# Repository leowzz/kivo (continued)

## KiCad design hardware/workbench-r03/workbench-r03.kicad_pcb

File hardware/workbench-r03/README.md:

# Kivo Workbench r03 PCB Draft

This is an editable electrical and placement draft, **not a board ready to
order**. Open `workbench-r03.kicad_pro` in KiCad 10. The PCB is intentionally
unrouted, and no Gerber, drill, or assembly-order files are provided.

## Confirmed Scope

- RP2040 chip directly on the main PCB, with factory assembly for the QFN.
- 18 ordinary MX switches with Kailh-style hot-swap sockets on the PCB back.
- USB-C for USB 2.0 device data and 5 V power.
- Existing SH1106, EC11, encoder press, confirm and back module connected by a
  harness. The module remains a separate panel-mounted assembly.
- Enclosure changes and reprinting are permitted.

The existing `r02` product YAML remains the source of the GPIO mapping. `r03`
here is a proposed new hardware revision, not a released Product Version ID.

## Files

| File | Purpose |
| --- | --- |
| `workbench-r03.kicad_sch` | Embedded-symbol schematic, 59 components |
| `workbench-r03.kicad_pcb` | Four-layer, 1.6 mm placement draft with 18 bottom sockets |
| `workbench-r03.kicad_pro` | KiCad project and preliminary design rules |
| `Workbench.pretty/` | Local hot-swap socket and measured-head mounting footprints |
| `key-coordinates.csv` | Model panel coordinates and PCB coordinates, in mm |
| `placement.json` | Reproducible placement and pin-to-net manifest |
| `bom-draft.csv` | Uncosted component list; not a factory purchasing BOM |
| `verification.md` | Checks performed and open issues |

## Electrical Design

The RP2040 core follows the Raspberry Pi hardware design guide: 3.3 V I/O,
the internal 1.1 V regulator feeding DVDD, TESTEN tied to ground, local bypass
capacitors, QSPI flash, and an external 12 MHz crystal. The proposed parts are:

| Function | Proposed part / connection |
| --- | --- |
| MCU | RP2040, QFN-56 with exposed ground pad |
| Flash | W25Q128JVSIQ, 128 Mbit / 16 MiB, 208 mil SOIC-8 |
| Crystal | Abracon ABM8-272-T3, 12 MHz, 15 pF loads, 1 kohm damping resistor |
| 3.3 V regulator | AP2112K-3.3TRG1, 1 uF input and 4.7 uF output |
| USB-C | GCT USB4105-GF-A, USB 2.0, separate 5.1 kohm CC1/CC2 pull-downs |
| USB data | USBLC6-2SC6 protection, 27 ohm series resistors near RP2040 |
| BOOTSEL | Push switch through 1 kohm to QSPI_SS; 10 kohm pull-up fitted |
| RESET | Push switch to RUN, with 10 kohm pull-up |
| Keys | Each GPIO to one socket contact; the other contact to GND |
| I2C pull-ups | R9/R10 4.7 kohm footprints, DNP pending module inspection |

Direct GPIO inputs use the existing firmware's pull-ups and debounce. This
topology does not need matrix diodes. The 16 MiB flash matches the current
YD-RP2040 build's maximum flash size. That does not, by itself, validate the
custom board's firmware identity or boot behavior.

These are proposed MPNs, not a stock-checked shopping list. In particular,
confirm the purchased socket's drawing against the vendored footprint, and
confirm the exact USB connector suffix, plating and packaging before ordering.
The PCB includes no microphone, speaker, battery, charger or RGB lighting.

## Main Board Interfaces

J2 is a **main-board harness pinout chosen for this PCB**. It is not evidence of
the left-to-right pin order of the purchased display module. Use individually
mapped wires and the module's labels; do not assume a straight-through cable.
The repository's YAML provides the GPIO assignments below, but does not record
the module connector numbering or power specification.

| J2 Pin | Main Board Signal | RP2040 GPIO |
| --- | --- | --- |
| 1 (square pad) | GND | - |
| 2 | 3.3 V | - |
| 3 | SCL | 27 |
| 4 | SDA | 26 |
| 5 | Confirm / OK | 22 |
| 6 | Encoder press | 28 |
| 7 | Encoder A | 21 |
| 8 | Encoder B | 20 |
| 9 | Back | 19 |

The main-board header is a 1x9, 2.54 mm pitch header. It is placed vertically
in the PCB top view with pin 1 closest to the USB edge. J2 provides **3.3 V only**;
verify the module operates at 3.3 V and that its signals and I2C pull-ups do not
drive 5 V into the RP2040. R9/R10 should be fitted only if the module lacks
suitable pull-ups. The guide's "seven GPIO" count excludes power and ground.

J3 pins 1-4 are 3.3 V reference, GND, SWDIO and SWCLK. A debugger should sense
the target voltage without powering a simultaneously USB-powered board.

J4 exposes all five unused RP2040 GPIOs at the **rear-left (upper-left in top
view)** of the PCB. It is a 1x7 plated through-hole header, 2.54 mm pitch with
1.0 mm drills. Viewed from the component side with USB at the top, pin 1 is
the leftmost square pad; the pins run left to right:

| J4 Pin | Signal |
| --- | --- |
| 1 (square pad) | GND |
| 2 | 3.3 V |
| 3 | GPIO0 |
| 4 | GPIO23 |
| 5 | GPIO24 |
| 6 | GPIO25 |
| 7 | GPIO29 / ADC3 |

These pins connect directly to the RP2040 and use **3.3 V logic, not 5 V**.
External loads must fit within the regulator's remaining current and thermal
budget. GPIO24/25 are free on this bare-chip design, but the current YD-RP2040
firmware pin whitelist excludes them. Enable them in the future custom-board
definition before use; this hardware change does not change the product
profile or assign functions to any expansion pins.

J5 (BOOT) and J6 (RESET) sit immediately to the left of the rear USB-C port.
Each is a 1x2 plated through-hole footprint, 2.54 mm pitch with 1.0 mm drills,
for a matching normally-open momentary button or short wires to a button.
They are not a universal four-leg tactile-switch footprint. Viewed from the
component side with USB at the top, pin 1 is the left square pad:

| Header | Pin 1 | Pin 2 | Connection |
| --- | --- | --- | --- |
| J5 BOOT | BOOT_BUTTON | GND | Parallel to SW19; through R7 (1 kohm) to QSPI_SS |
| J6 RESET | RUN | GND | Parallel to SW20; R8 (10 kohm) pulls RUN up to 3.3 V |

The onboard SW19/SW20 buttons remain fitted. To enter the USB bootloader,
hold BOOT, press and release RESET, then release BOOT. Do not short QSPI_SS
directly to ground; J5 preserves the existing series resistor.

K1-K18 retain GPIO1-GPIO18. Viewed from the key side with USB at the back,
K1-K6 are the row closest to the display, K7-K12 are the middle row, and K13-K18
are closest to the user. The geometry script does not assign key IDs; this
numbering follows the current product layout's reading order.

## Mechanical Basis

Source: `scripts/modeling/integrated_workstation.py`, specifically
`KEY_COLUMNS`, `KEY_ROWS`, `KEY_PITCH`, `KEY_X0`, `KEY_Y0`, `PANEL_X0`, and
`PANEL_Y0`. The generated switch centers use the **flat panel plane**, not a
top-down projection of its 30-degree assembled position.

- Existing panel: 132 x 117 mm, tilted 30 degrees.
- Proposed board: 126 x 105 mm, 1.6 mm thick, parallel to the panel.
- Model panel coordinates: X to the right, Y from the front towards the rear.
- Board coordinates in CSV: origin at the board's rear-left corner, X right,
  Y towards the user. Conversion: `pcb_x = panel_x - 3`,
  `pcb_y = 113 - panel_y`.
- The KiCad page uses an additional (50, 50) mm translation for readability.
- 19.05 mm switch pitch is preserved. The five 3.4 mm PCB holes are **new**
  proposed mounting positions; they do not reuse the existing panel screw axes.
- The local mounting footprint assumes a screw head no larger than 5.6 mm,
  with a 6.0 mm clearance envelope and no large washer. This follows the
  project's measured 5.3 mm head, but actual fasteners and bosses need checking.

The current shell has two solid support walls in the key field, six fly-wire
clips, a bottom-mounted development-board cradle and low rear USB openings.
These features require redesign around the new board. The existing two-switch
pod also needs a decision during the enclosure revision because it is absent
from the current product's electrical configuration.

The `Dwgs.User` display rectangle is a reserved area, not a validated 3D module
model. Before final PCB dimensions, verify the switch plate-to-PCB distance,
socket underside height, display connector height, panel screw access and USB
plug insertion. Include the J4 header/mating connector height near the display
and the J5/J6 button or wire clearance in the enclosure check. The new USB port
follows the sloped board and cannot align with
the old bottom-board USB opening. The existing eight-pin modeling constant is
inconsistent with the apparent nine contacts in `refer/dsp-encp.png`; keep the
electrical harness independent of that mechanical assumption.

## Remaining Design Work

1. Verify the actual display module's voltage, connector labels and pull-ups,
   and the exact socket and USB connector drawings.
2. Establish a manufacturer stackup and impedance geometry. The four-layer
   board is proposed to give USB and the RP2040 a continuous reference plane;
   the current layer count is not a validated impedance specification.
3. Complete placement for short crystal, QSPI, regulator and decoupling paths,
   then route, pour ground planes and rerun DRC. Keep the USB pair over continuous
   ground and determine widths/gap for 90 ohm differential impedance from the
   selected stackup. Review QFN ground and paste/thermal-via assembly details.
4. Revise and collision-check the enclosure in 3D, including MX plate capture
   thickness, new PCB mounts and the USB opening. Existing STLs are unchanged.
5. Add the new board identity/build target and an r03 product definition when
   the electrical design is frozen; validate USB descriptors, flash size,
   BOOTSEL, reset, HID/CDC, all 18 keys, display and controls on assembled boards.
6. Select purchasable parts, complete ERC/DRC and assembly review, and then
   export Gerbers, drill files, BOM and placement files for the board house.

## Reproduction

The checked-in KiCad files are the editable design. The generators are a way to
reproduce this first draft, not a substitute for the PCB editor. Generate into a
new directory to preserve manual changes:

```sh
uv run --script scripts/hardware/generate_workbench.py --output /tmp/workbench-review
```

Copy `Workbench.pretty`, `3dmodels`, `fp-lib-table` and the project settings from
this directory into that new directory, then run the placement script using
KiCad's bundled Python interpreter:

```sh
/Applications/KiCad/KiCad.app/Contents/Frameworks/Python.framework/Versions/3.9/bin/python3.9 \
  scripts/hardware/place_workbench.py /tmp/workbench-review/placement.json \
  /tmp/workbench-review/workbench-r03.kicad_pcb
```

The placement script refuses to overwrite an existing PCB. Both scripts accept
explicit library paths for KiCad installations at other locations.

## Sources

- Existing product: `products/kivo-workbench-rp-k18-disp-encp-r02/product.yaml`.
- [Raspberry Pi Hardware Design with RP2040](https://datasheets.raspberrypi.com/rp2040/hardware-design-with-rp2040.pdf), release 2,
  sections 2.1-2.4. The source reference design's routing was not transplanted.
- [foostan/kbd MX hot-swap footprint](https://github.com/foostan/kbd/blob/main/kicad-footprints/kbd.pretty/keyswitch_cherrymx_hotswap_1u.kicad_mod),
  retrieved 2026-09-05, upstream blob `3601d4e1d8f8c5b49b9d56c87e00ec56cd4921a1`.
  Only its 3D-model path was changed. The matching socket STEP model is vendored
  from the same repository. License: `licenses/foostan-kbd-MIT.txt`.
- Standard electronic symbols, packages and 3D models come from installed
  KiCad 10.0.6 libraries. The schematic embeds the symbols for portability.

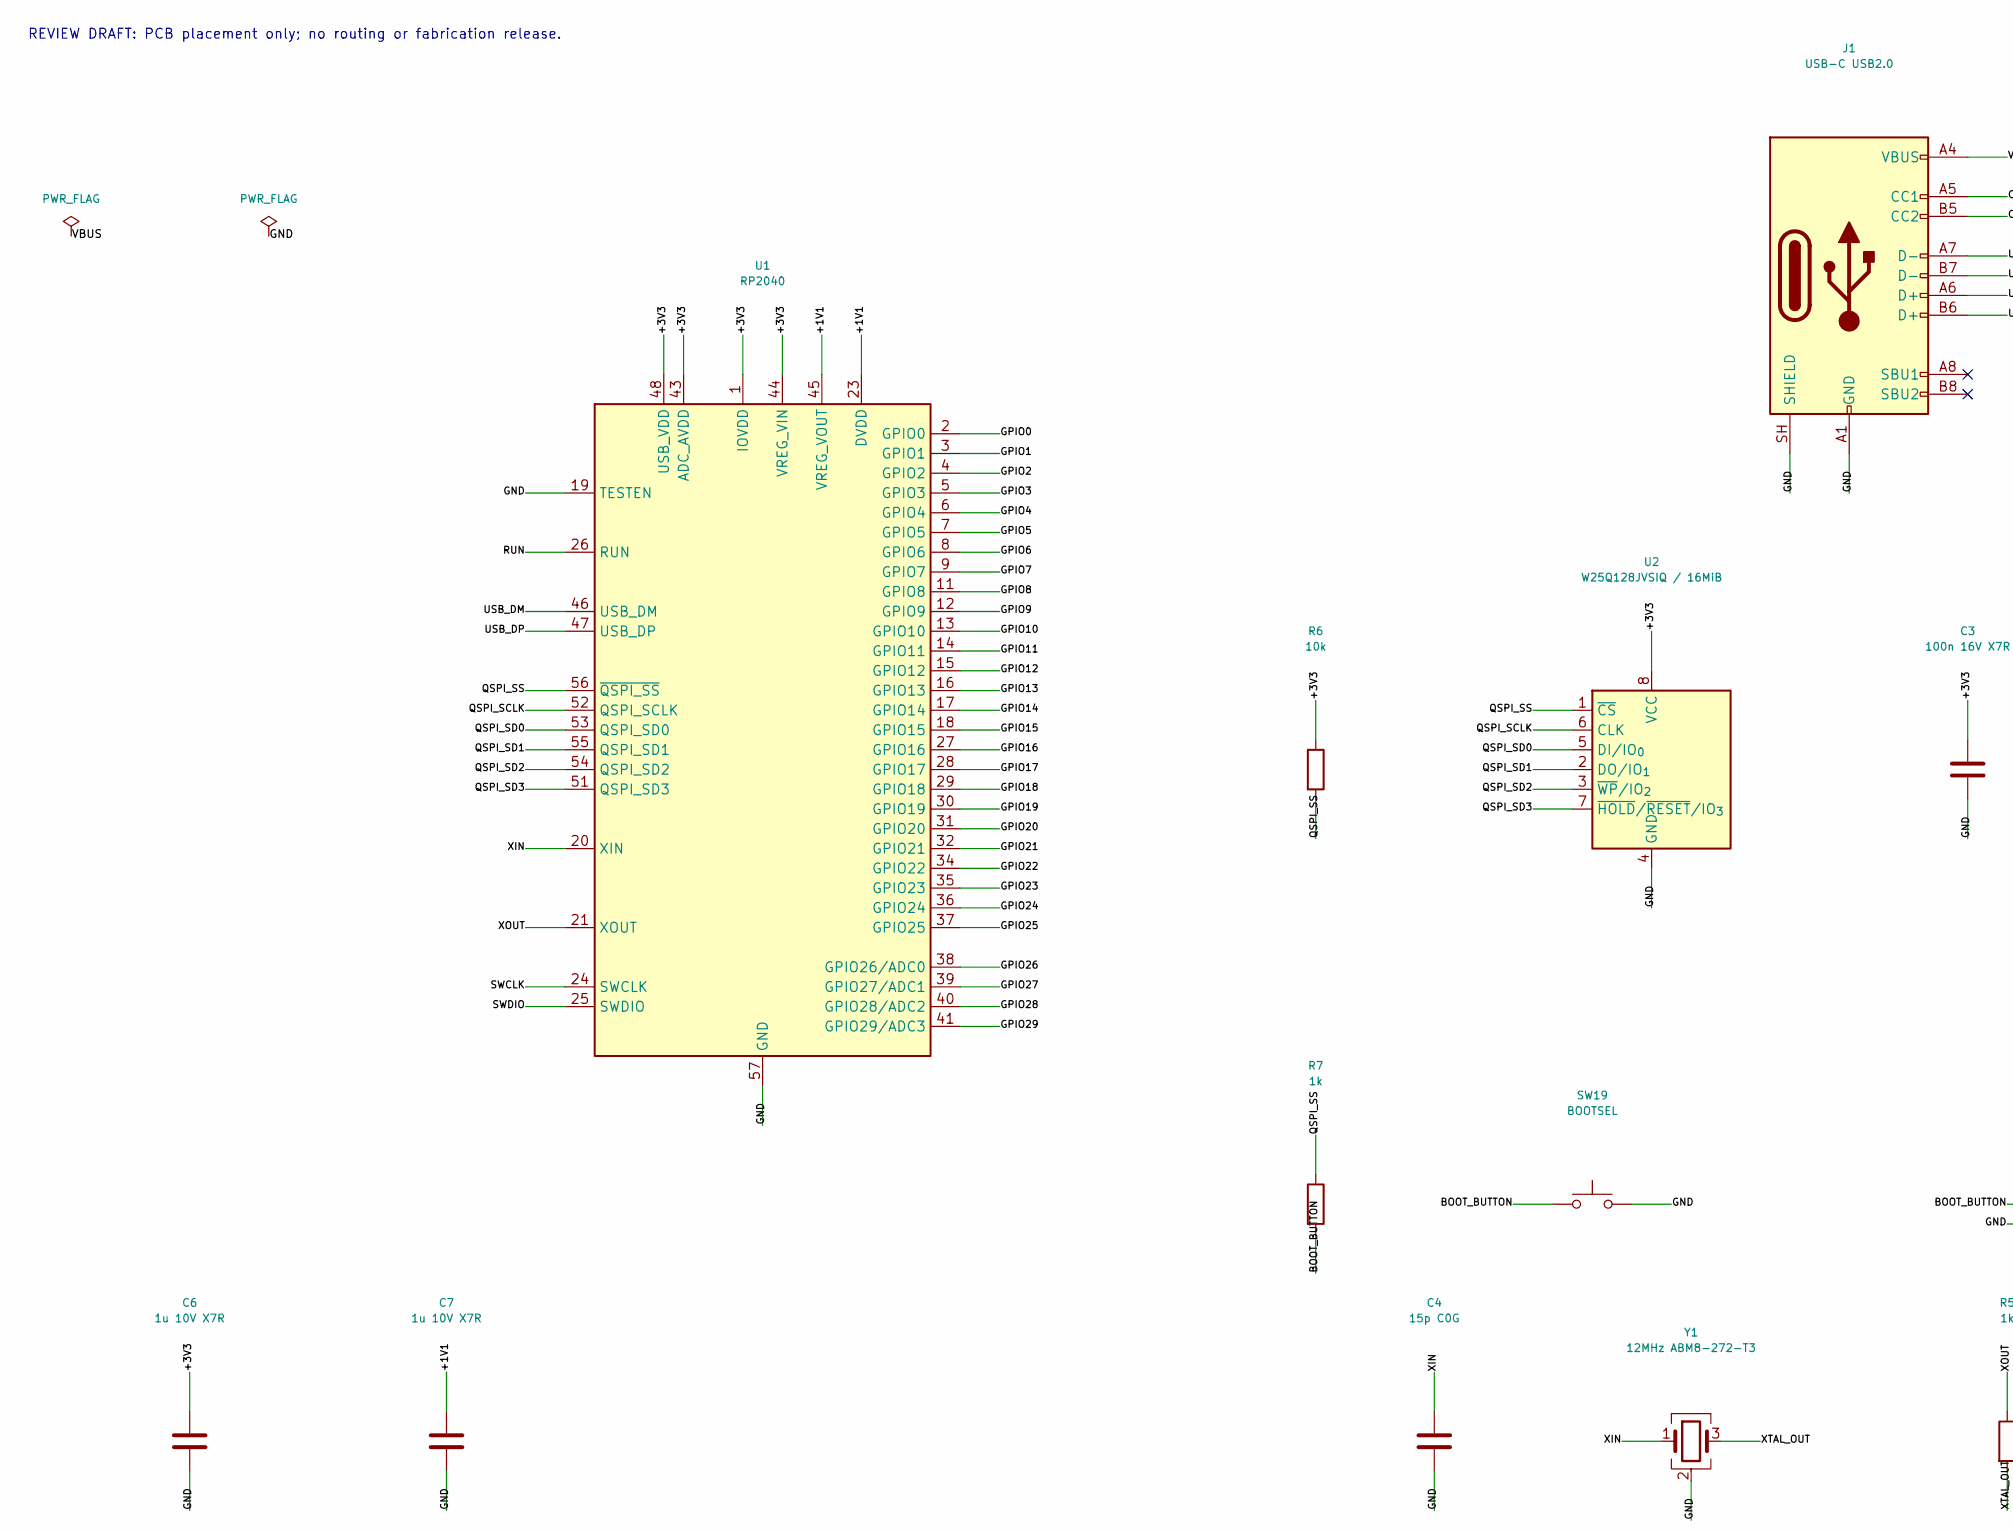
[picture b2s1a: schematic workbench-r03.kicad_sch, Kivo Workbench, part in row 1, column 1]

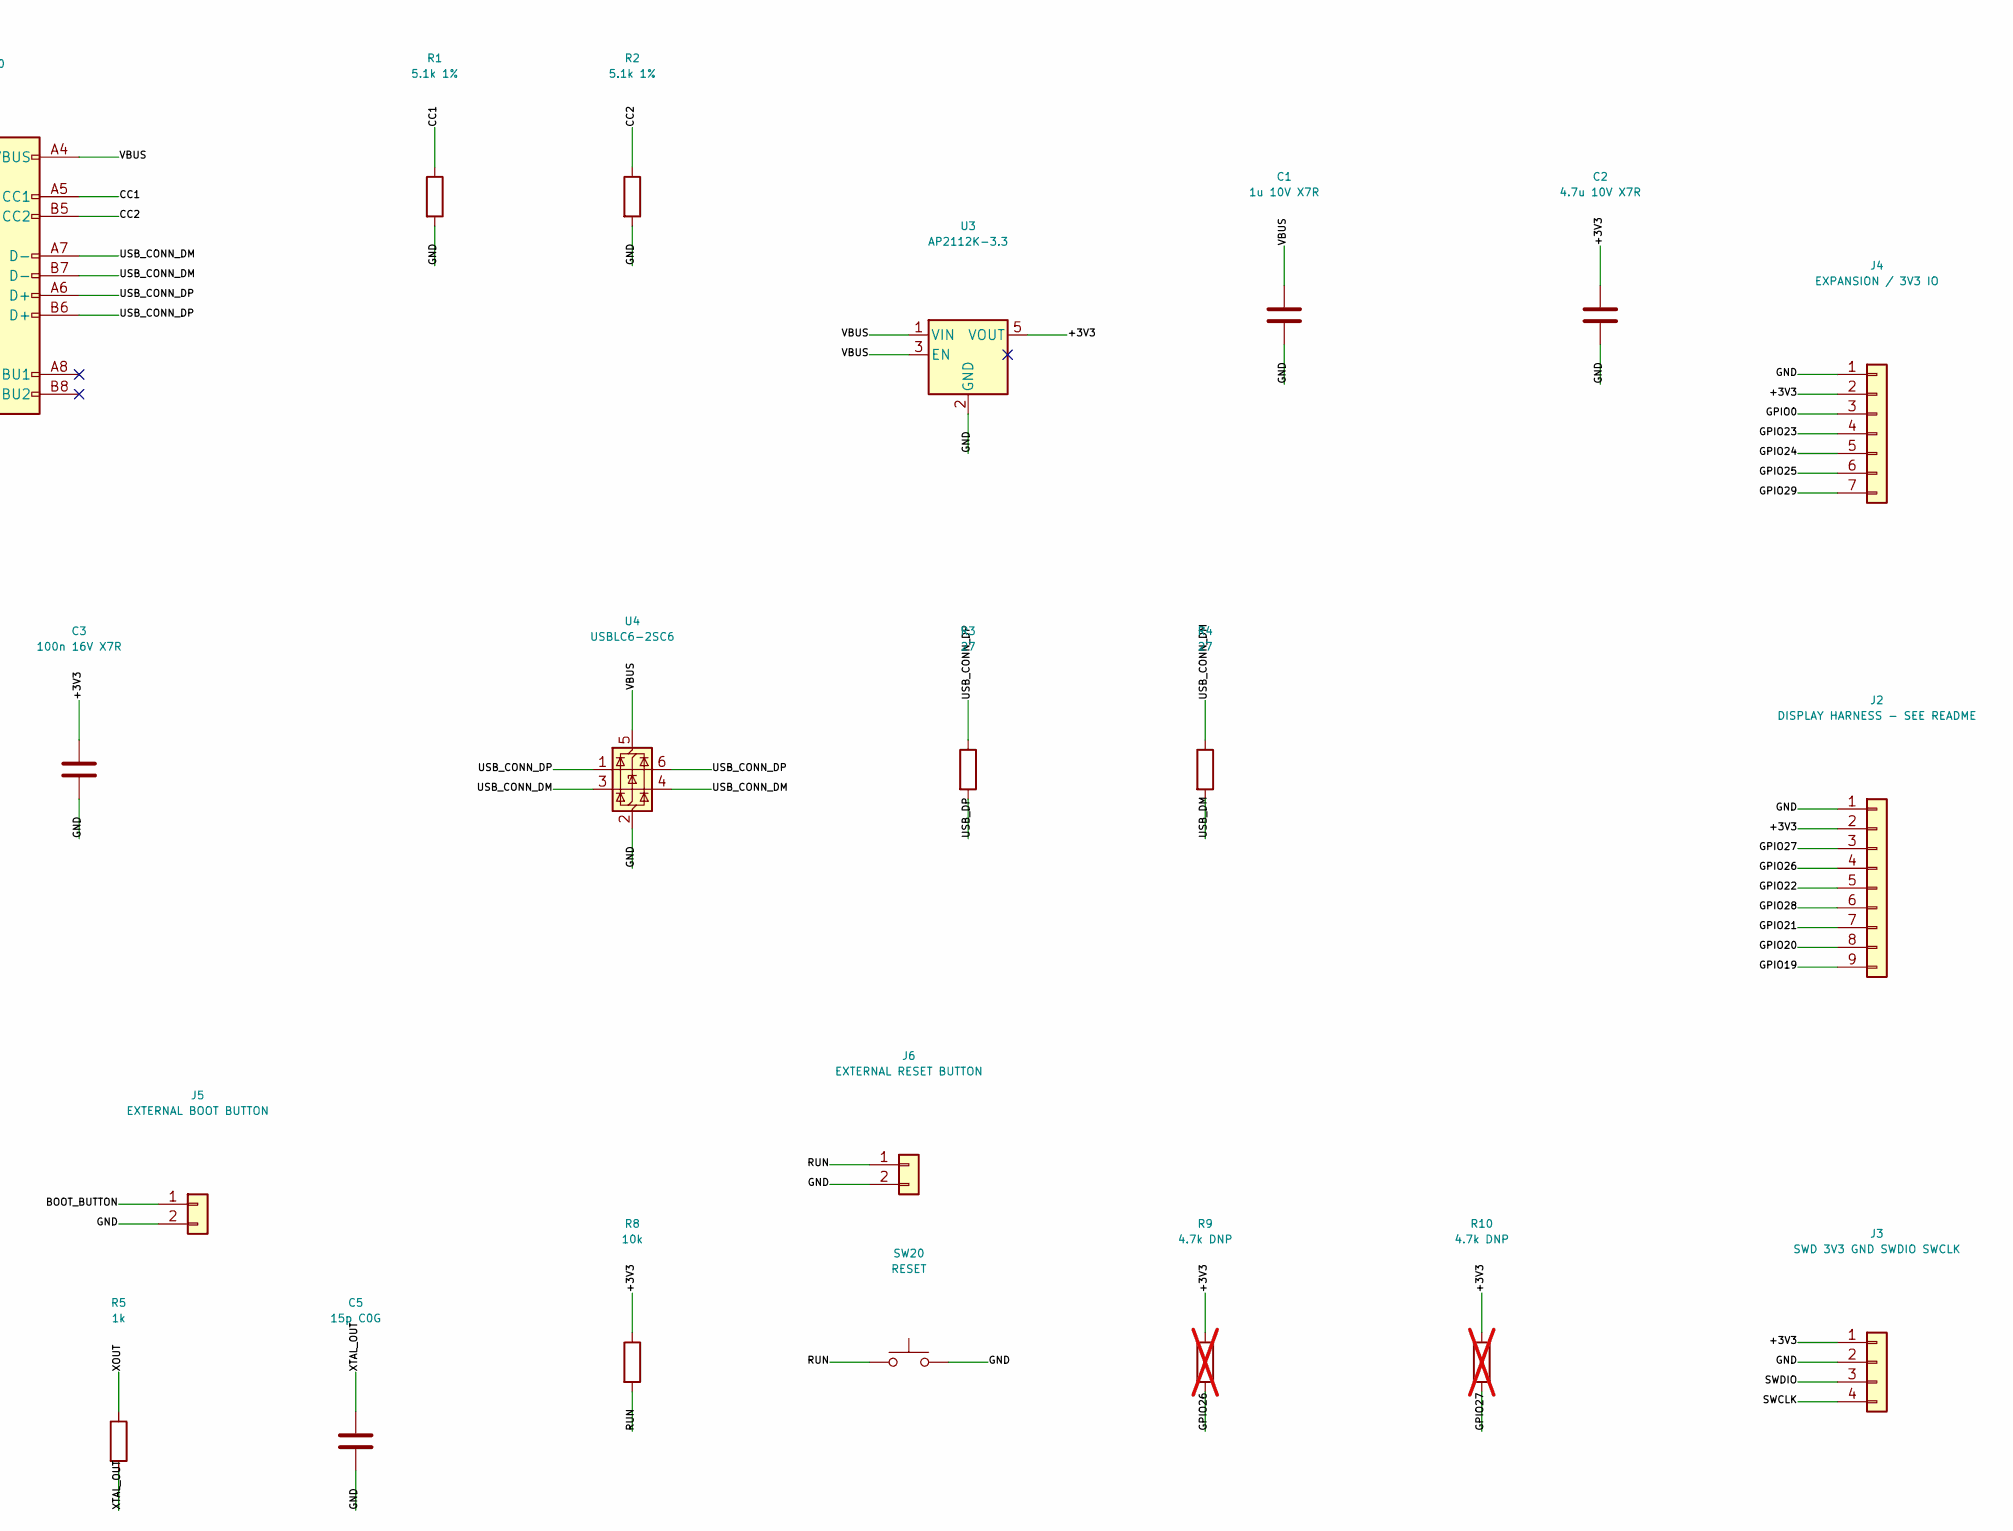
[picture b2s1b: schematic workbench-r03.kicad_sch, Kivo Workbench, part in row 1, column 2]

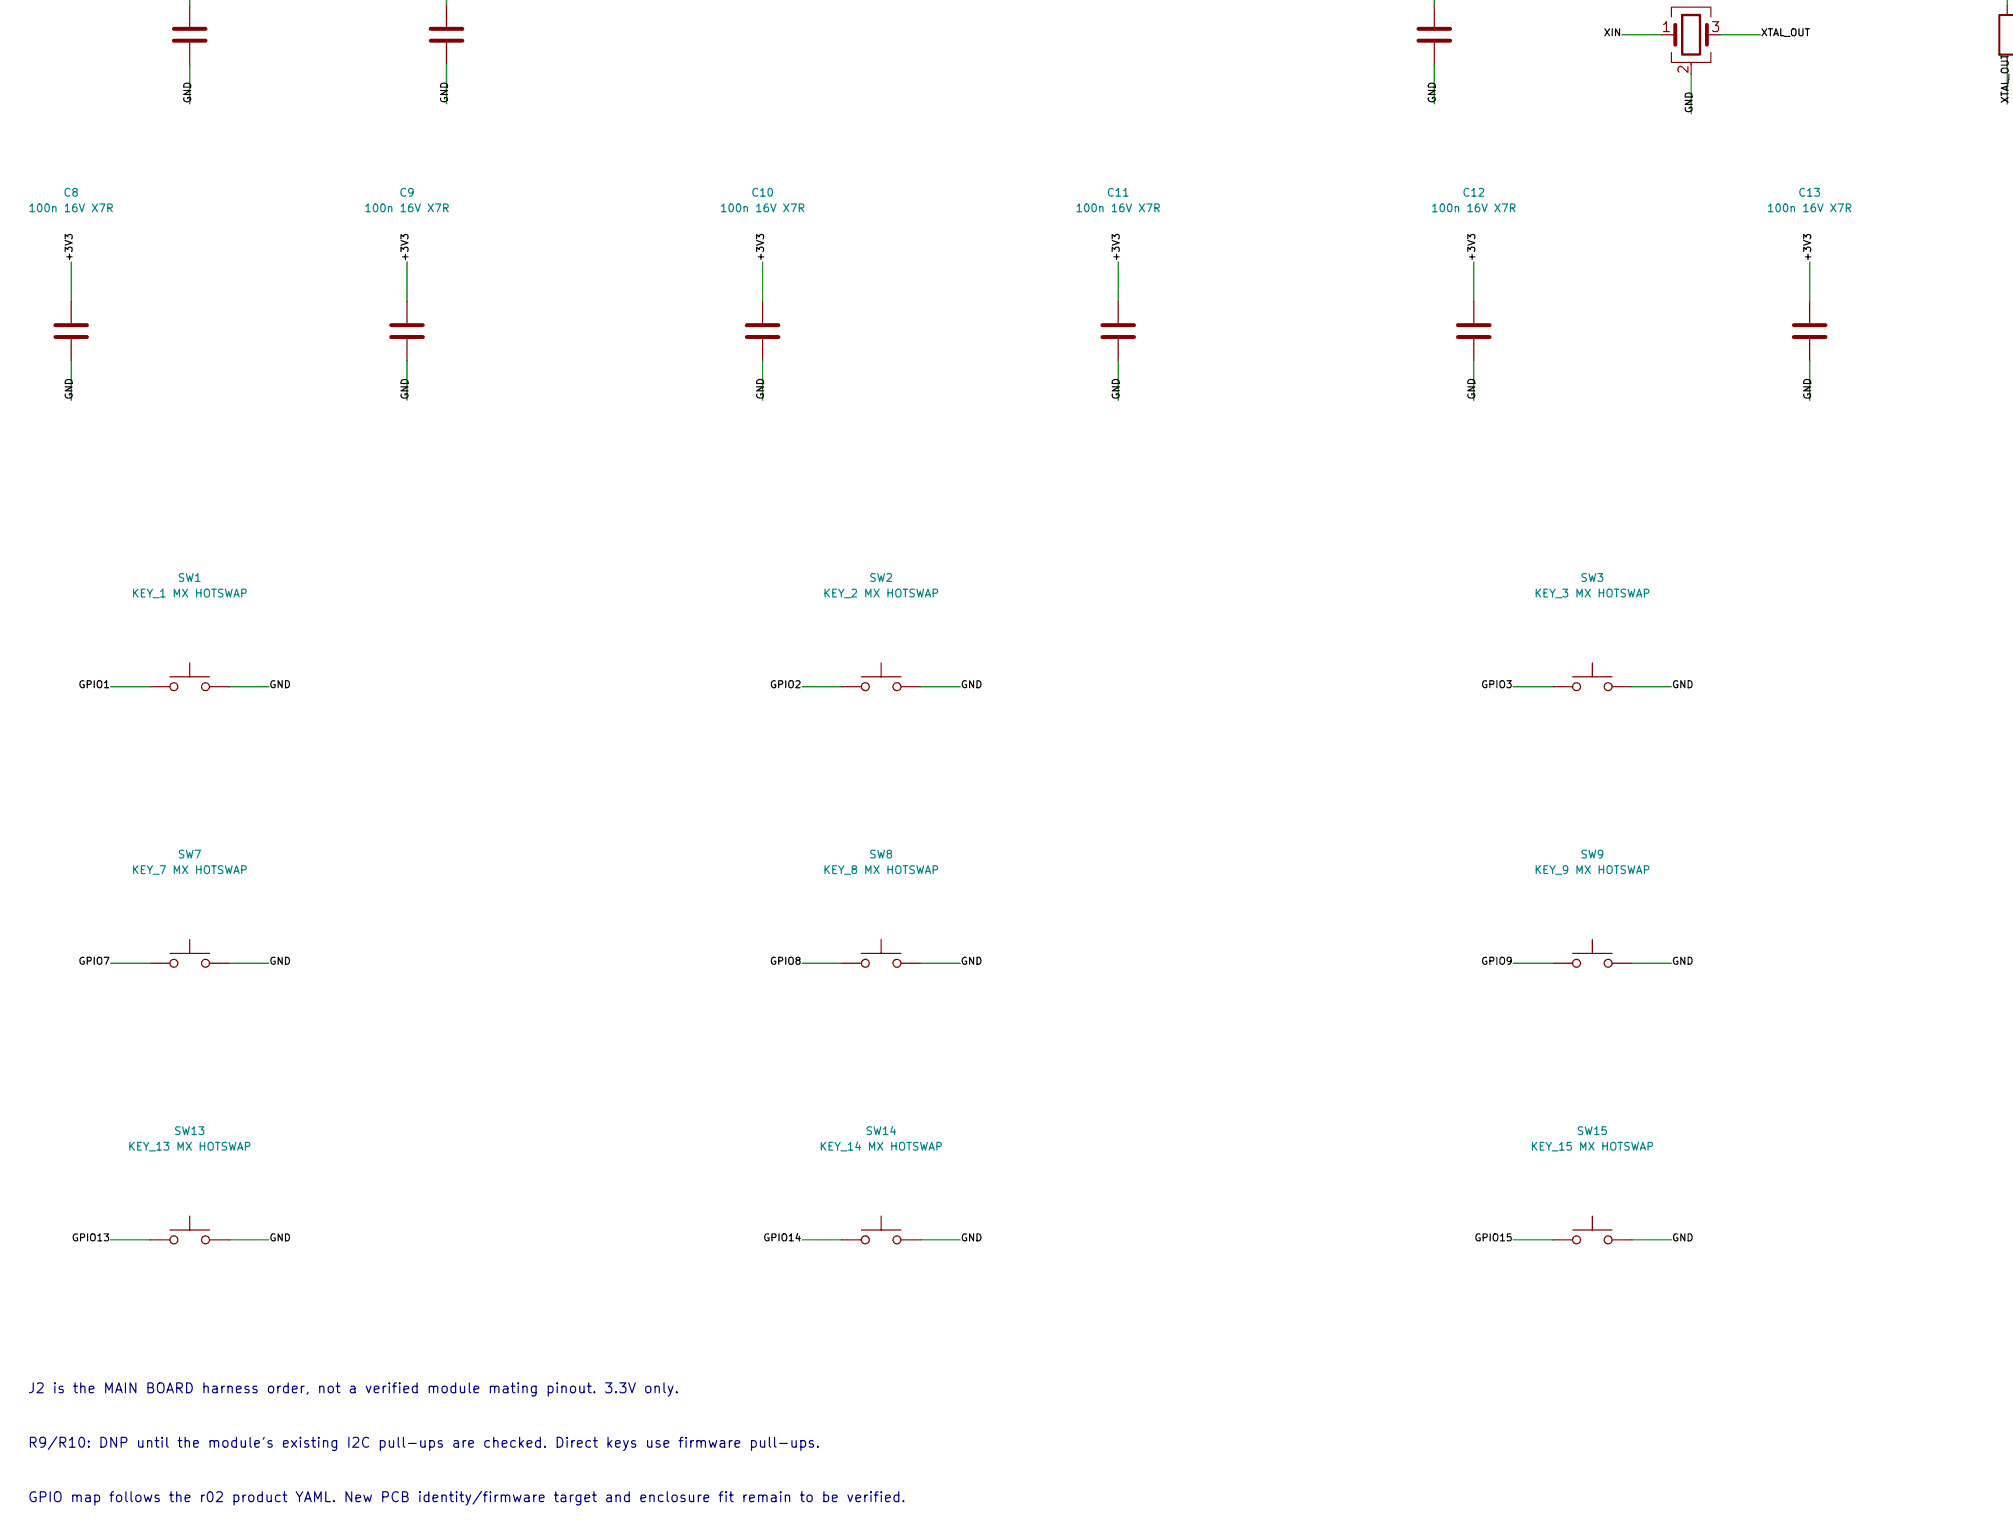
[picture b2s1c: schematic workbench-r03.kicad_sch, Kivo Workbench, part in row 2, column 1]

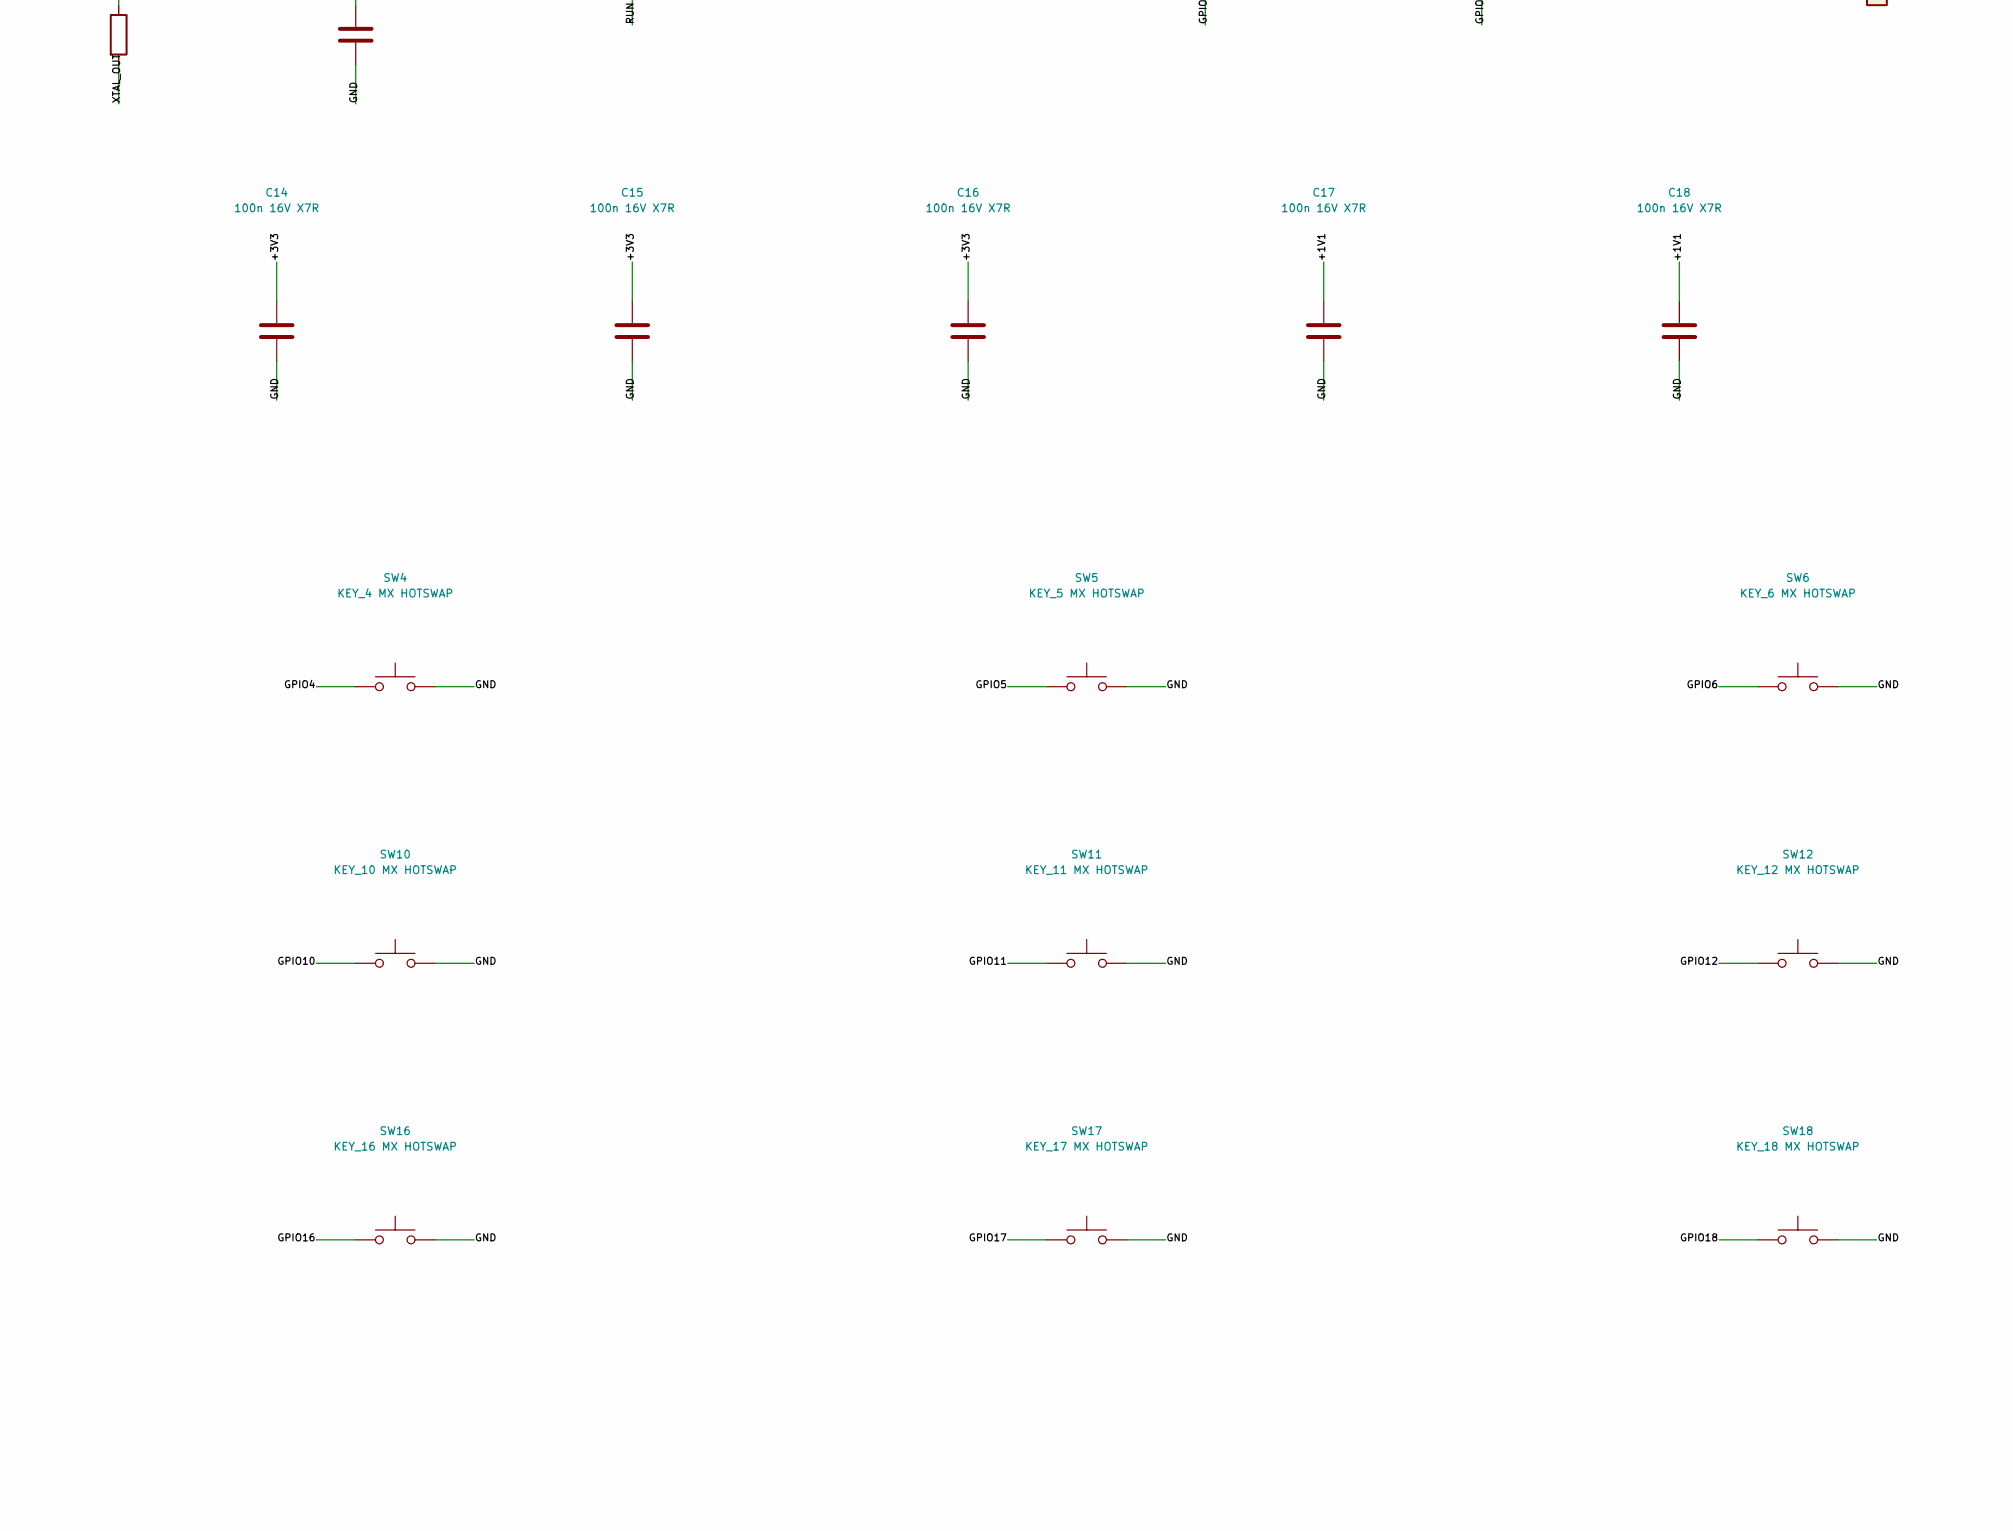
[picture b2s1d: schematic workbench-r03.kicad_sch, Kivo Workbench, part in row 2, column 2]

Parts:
C1: 1u 10V X7R; C_0603_1608Metric
C2: 4.7u 10V X7R; C_0603_1608Metric
C3, C8, C9, C10, C11, C12, C13, C14, C15, C16, C17, C18: 100n 16V X7R; C_0402_1005Metric
C4, C5: 15p C0G; C_0402_1005Metric
C6, C7: 1u 10V X7R; C_0402_1005Metric
J1: USB-C USB2.0; USB_C_Receptacle_GCT_USB4105-xx-A_16P_TopMnt_Horizontal
J2: DISPLAY HARNESS - SEE README; PinHeader_1x09_P2.54mm_Vertical
J3: SWD 3V3 GND SWDIO SWCLK; PinHeader_1x04_P2.54mm_Vertical
J4: EXPANSION / 3V3 IO; PinHeader_1x07_P2.54mm_Vertical
J5: EXTERNAL BOOT BUTTON; PinHeader_1x02_P2.54mm_Vertical
J6: EXTERNAL RESET BUTTON; PinHeader_1x02_P2.54mm_Vertical
R1, R2: 5.1k 1%; R_0603_1608Metric
R3, R4: 27; R_0603_1608Metric
R5, R7: 1k; R_0603_1608Metric
R6, R8: 10k; R_0603_1608Metric
R9, R10: 4.7k DNP; R_0603_1608Metric; not fitted
SW1: KEY_1 MX HOTSWAP; keyswitch_cherrymx_hotswap_1u
SW2: KEY_2 MX HOTSWAP; keyswitch_cherrymx_hotswap_1u
SW3: KEY_3 MX HOTSWAP; keyswitch_cherrymx_hotswap_1u
SW4: KEY_4 MX HOTSWAP; keyswitch_cherrymx_hotswap_1u
SW5: KEY_5 MX HOTSWAP; keyswitch_cherrymx_hotswap_1u
SW6: KEY_6 MX HOTSWAP; keyswitch_cherrymx_hotswap_1u
SW7: KEY_7 MX HOTSWAP; keyswitch_cherrymx_hotswap_1u
SW8: KEY_8 MX HOTSWAP; keyswitch_cherrymx_hotswap_1u
SW9: KEY_9 MX HOTSWAP; keyswitch_cherrymx_hotswap_1u
SW10: KEY_10 MX HOTSWAP; keyswitch_cherrymx_hotswap_1u
SW11: KEY_11 MX HOTSWAP; keyswitch_cherrymx_hotswap_1u
SW12: KEY_12 MX HOTSWAP; keyswitch_cherrymx_hotswap_1u
SW13: KEY_13 MX HOTSWAP; keyswitch_cherrymx_hotswap_1u
SW14: KEY_14 MX HOTSWAP; keyswitch_cherrymx_hotswap_1u
SW15: KEY_15 MX HOTSWAP; keyswitch_cherrymx_hotswap_1u
SW16: KEY_16 MX HOTSWAP; keyswitch_cherrymx_hotswap_1u
SW17: KEY_17 MX HOTSWAP; keyswitch_cherrymx_hotswap_1u
SW18: KEY_18 MX HOTSWAP; keyswitch_cherrymx_hotswap_1u
SW19: BOOTSEL; SW_SPST_TL3342
SW20: RESET; SW_SPST_TL3342
U1: RP2040; QFN-56-1EP_7x7mm_P0.4mm_EP3.2x3.2mm
U2: W25Q128JVSIQ / 16MiB; SOIC-8_5.3x5.3mm_P1.27mm
U3: AP2112K-3.3; SOT-23-5
U4: USBLC6-2SC6; SOT-23-6
Y1: 12MHz ABM8-272-T3; Crystal_SMD_3225-4Pin_3.2x2.5mm

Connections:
/+1V1: C7.1, C17.1, C18.1, U1.23 (DVDD), U1.45 (VREG_VOUT), U1.50 (DVDD)
/+3V3: C2.1, C3.1, C6.1, C8.1, C9.1, C10.1, C11.1, C12.1, C13.1, C14.1, C15.1, C16.1, J2.2, J3.1, J4.2, R6.1, R8.1, R9.1, R10.1, U1.1 (IOVDD), U1.10 (IOVDD), U1.22 (IOVDD), U1.33 (IOVDD), U1.42 (IOVDD), U1.43 (ADC_AVDD), U1.44 (VREG_VIN), U1.48 (USB_VDD), U1.49 (IOVDD), U2.8 (VCC), U3.5 (VOUT)
/BOOT_BUTTON: J5.1, R7.2, SW19.1
/CC1: J1.A5 (CC1), R1.1
/CC2: J1.B5 (CC2), R2.1
/GND: C1.2, C2.2, C3.2, C4.2, C5.2, C6.2, C7.2, C8.2, C9.2, C10.2, C11.2, C12.2, C13.2, C14.2, C15.2, C16.2, C17.2, C18.2, J1.A1 (GND), J1.A12 (GND), J1.B1 (GND), J1.B12 (GND), J1.SH (SHIELD), J2.1, J3.2, J4.1, J5.2, J6.2, R1.2, R2.2, SW1.2, SW2.2, SW3.2, SW4.2, SW5.2, SW6.2, SW7.2, SW8.2, SW9.2, SW10.2, SW11.2, SW12.2, SW13.2, SW14.2, SW15.2, SW16.2, SW17.2, SW18.2, SW19.2, SW20.2, U1.19 (TESTEN), U1.57 (GND), U2.4 (GND), U3.2 (GND), U4.2 (GND), Y1.2 (G), Y1.4 (G)
/GPIO0: J4.3, U1.2 (GPIO0)
/GPIO1: SW1.1, U1.3 (GPIO1)
/GPIO2: SW2.1, U1.4 (GPIO2)
/GPIO3: SW3.1, U1.5 (GPIO3)
/GPIO4: SW4.1, U1.6 (GPIO4)
/GPIO5: SW5.1, U1.7 (GPIO5)
/GPIO6: SW6.1, U1.8 (GPIO6)
/GPIO7: SW7.1, U1.9 (GPIO7)
/GPIO8: SW8.1, U1.11 (GPIO8)
/GPIO9: SW9.1, U1.12 (GPIO9)
/GPIO10: SW10.1, U1.13 (GPIO10)
/GPIO11: SW11.1, U1.14 (GPIO11)
/GPIO12: SW12.1, U1.15 (GPIO12)
/GPIO13: SW13.1, U1.16 (GPIO13)
/GPIO14: SW14.1, U1.17 (GPIO14)
/GPIO15: SW15.1, U1.18 (GPIO15)
/GPIO16: SW16.1, U1.27 (GPIO16)
/GPIO17: SW17.1, U1.28 (GPIO17)
/GPIO18: SW18.1, U1.29 (GPIO18)
/GPIO19: J2.9, U1.30 (GPIO19)
/GPIO20: J2.8, U1.31 (GPIO20)
/GPIO21: J2.7, U1.32 (GPIO21)
/GPIO22: J2.5, U1.34 (GPIO22)
/GPIO23: J4.4, U1.35 (GPIO23)
/GPIO24: J4.5, U1.36 (GPIO24)
/GPIO25: J4.6, U1.37 (GPIO25)
/GPIO26: J2.4, R9.2, U1.38 (GPIO26/ADC0)
/GPIO27: J2.3, R10.2, U1.39 (GPIO27/ADC1)
/GPIO28: J2.6, U1.40 (GPIO28/ADC2)
/GPIO29: J4.7, U1.41 (GPIO29/ADC3)
/QSPI_SCLK: U1.52 (QSPI_SCLK), U2.6 (CLK)
/QSPI_SD0: U1.53 (QSPI_SD0), U2.5 (DI/IO_{0})
/QSPI_SD1: U1.55 (QSPI_SD1), U2.2 (DO/IO_{1})
/QSPI_SD2: U1.54 (QSPI_SD2), U2.3 (~WP/IO_{2})
/QSPI_SD3: U1.51 (QSPI_SD3), U2.7 (~HOLD/~RESET/IO_{3})
/QSPI_SS: R6.2, R7.1, U1.56 (~QSPI_SS), U2.1 (~CS)
/RUN: J6.1, R8.2, SW20.1, U1.26 (RUN)
/SWCLK: J3.4, U1.24 (SWCLK)
/SWDIO: J3.3, U1.25 (SWDIO)
/USB_CONN_DM: J1.A7 (D-), J1.B7 (D-), R4.1, U4.3 (I/O2), U4.4 (I/O2)
/USB_CONN_DP: J1.A6 (D+), J1.B6 (D+), R3.1, U4.1 (I/O1), U4.6 (I/O1)
/USB_DM: R4.2, U1.46 (USB_DM)
/USB_DP: R3.2, U1.47 (USB_DP)
/VBUS: C1.1, J1.A4 (VBUS), J1.A9 (VBUS), J1.B4 (VBUS), J1.B9 (VBUS), U3.1 (VIN), U3.3 (EN), U4.5 (VBUS)
/XIN: C4.1, U1.20 (XIN), Y1.1
/XOUT: R5.1, U1.21 (XOUT)
/XTAL_OUT: C5.1, R5.2, Y1.3

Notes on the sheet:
REVIEW DRAFT: PCB placement only; no routing or fabrication release.
J2 is the MAIN BOARD harness order, not a verified module mating pinout. 3.3V only.
R9/R10: DNP until the module's existing I2C pull-ups are checked. Direct keys use firmware pull-ups.
GPIO map follows the r02 product YAML. New PCB identity/firmware target and enclosure fit remain to be verified.

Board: 4 copper layers, 64 parts (18 on the bottom side), 53 nets, no tracks yet.

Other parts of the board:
H1, H2, H3, H4, H5: M3 head <=5.6mm; MountingHole_M3_5.6mm_Head

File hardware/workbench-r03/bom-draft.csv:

Reference,Value,Footprint,MPN,DNP
U1,RP2040,Package_DFN_QFN:QFN-56-1EP_7x7mm_P0.4mm_EP3.2x3.2mm,RP2040,False
U2,W25Q128JVSIQ / 16MiB,Package_SO:SOIC-8_5.3x5.3mm_P1.27mm,W25Q128JVSIQ,False
U3,AP2112K-3.3,Package_TO_SOT_SMD:SOT-23-5,AP2112K-3.3TRG1,False
J1,USB-C USB2.0,Connector_USB:USB_C_Receptacle_GCT_USB4105-xx-A_16P_TopMnt_Horizontal,GCT USB4105-GF-A,False
U4,USBLC6-2SC6,Package_TO_SOT_SMD:SOT-23-6,USBLC6-2SC6,False
Y1,12MHz ABM8-272-T3,Crystal:Crystal_SMD_3225-4Pin_3.2x2.5mm,ABM8-272-T3,False
R1,5.1k 1%,Resistor_SMD:R_0603_1608Metric,,False
R2,5.1k 1%,Resistor_SMD:R_0603_1608Metric,,False
R3,27,Resistor_SMD:R_0603_1608Metric,,False
R4,27,Resistor_SMD:R_0603_1608Metric,,False
R5,1k,Resistor_SMD:R_0603_1608Metric,,False
R6,10k,Resistor_SMD:R_0603_1608Metric,,False
R7,1k,Resistor_SMD:R_0603_1608Metric,,False
R8,10k,Resistor_SMD:R_0603_1608Metric,,False
R9,4.7k DNP,Resistor_SMD:R_0603_1608Metric,,True
R10,4.7k DNP,Resistor_SMD:R_0603_1608Metric,,True
C1,1u 10V X7R,Capacitor_SMD:C_0603_1608Metric,,False
C2,4.7u 10V X7R,Capacitor_SMD:C_0603_1608Metric,,False
C3,100n 16V X7R,Capacitor_SMD:C_0402_1005Metric,,False
C4,15p C0G,Capacitor_SMD:C_0402_1005Metric,,False
C5,15p C0G,Capacitor_SMD:C_0402_1005Metric,,False
C6,1u 10V X7R,Capacitor_SMD:C_0402_1005Metric,,False
C7,1u 10V X7R,Capacitor_SMD:C_0402_1005Metric,,False
C8,100n 16V X7R,Capacitor_SMD:C_0402_1005Metric,,False
C9,100n 16V X7R,Capacitor_SMD:C_0402_1005Metric,,False
C10,100n 16V X7R,Capacitor_SMD:C_0402_1005Metric,,False
C11,100n 16V X7R,Capacitor_SMD:C_0402_1005Metric,,False
C12,100n 16V X7R,Capacitor_SMD:C_0402_1005Metric,,False
C13,100n 16V X7R,Capacitor_SMD:C_0402_1005Metric,,False
C14,100n 16V X7R,Capacitor_SMD:C_0402_1005Metric,,False
C15,100n 16V X7R,Capacitor_SMD:C_0402_1005Metric,,False
C16,100n 16V X7R,Capacitor_SMD:C_0402_1005Metric,,False
C17,100n 16V X7R,Capacitor_SMD:C_0402_1005Metric,,False
C18,100n 16V X7R,Capacitor_SMD:C_0402_1005Metric,,False
SW19,BOOTSEL,Button_Switch_SMD:SW_SPST_TL3342,,False
SW20,RESET,Button_Switch_SMD:SW_SPST_TL3342,,False
J2,DISPLAY HARNESS - SEE README,Connector_PinHeader_2.54mm:PinHeader_1x09_P2.54mm_Vertical,,False
J3,SWD 3V3 GND SWDIO SWCLK,Connector_PinHeader_2.54mm:PinHeader_1x04_P2.54mm_Vertical,,False
J4,EXPANSION / 3V3 IO,Connector_PinHeader_2.54mm:PinHeader_1x07_P2.54mm_Vertical,,False
J5,EXTERNAL BOOT BUTTON,Connector_PinHeader_2.54mm:PinHeader_1x02_P2.54mm_Vertical,,False
J6,EXTERNAL RESET BUTTON,Connector_PinHeader_2.54mm:PinHeader_1x02_P2.54mm_Vertical,,False
SW1,KEY_1 MX HOTSWAP,Workbench:keyswitch_cherrymx_hotswap_1u,,False
SW2,KEY_2 MX HOTSWAP,Workbench:keyswitch_cherrymx_hotswap_1u,,False
SW3,KEY_3 MX HOTSWAP,Workbench:keyswitch_cherrymx_hotswap_1u,,False
SW4,KEY_4 MX HOTSWAP,Workbench:keyswitch_cherrymx_hotswap_1u,,False
SW5,KEY_5 MX HOTSWAP,Workbench:keyswitch_cherrymx_hotswap_1u,,False
SW6,KEY_6 MX HOTSWAP,Workbench:keyswitch_cherrymx_hotswap_1u,,False
SW7,KEY_7 MX HOTSWAP,Workbench:keyswitch_cherrymx_hotswap_1u,,False
SW8,KEY_8 MX HOTSWAP,Workbench:keyswitch_cherrymx_hotswap_1u,,False
SW9,KEY_9 MX HOTSWAP,Workbench:keyswitch_cherrymx_hotswap_1u,,False
SW10,KEY_10 MX HOTSWAP,Workbench:keyswitch_cherrymx_hotswap_1u,,False
SW11,KEY_11 MX HOTSWAP,Workbench:keyswitch_cherrymx_hotswap_1u,,False
SW12,KEY_12 MX HOTSWAP,Workbench:keyswitch_cherrymx_hotswap_1u,,False
SW13,KEY_13 MX HOTSWAP,Workbench:keyswitch_cherrymx_hotswap_1u,,False
SW14,KEY_14 MX HOTSWAP,Workbench:keyswitch_cherrymx_hotswap_1u,,False
SW15,KEY_15 MX HOTSWAP,Workbench:keyswitch_cherrymx_hotswap_1u,,False
SW16,KEY_16 MX HOTSWAP,Workbench:keyswitch_cherrymx_hotswap_1u,,False
SW17,KEY_17 MX HOTSWAP,Workbench:keyswitch_cherrymx_hotswap_1u,,False
SW18,KEY_18 MX HOTSWAP,Workbench:keyswitch_cherrymx_hotswap_1u,,False
